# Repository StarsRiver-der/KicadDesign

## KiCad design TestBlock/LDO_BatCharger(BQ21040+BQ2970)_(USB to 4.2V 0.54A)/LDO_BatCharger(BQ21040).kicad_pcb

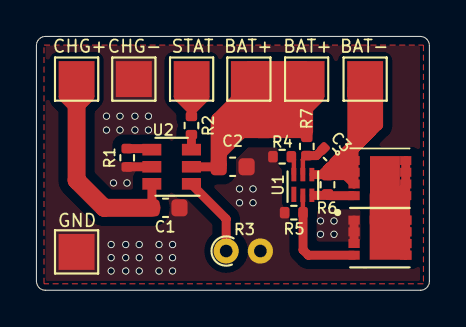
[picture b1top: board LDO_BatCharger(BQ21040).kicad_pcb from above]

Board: 2 copper layers, 21.8 x 14.1 mm, 21 parts (0 on the bottom side), 13 nets.

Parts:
C1, C2: 1uF; C_0603_1608Metric
C3: 0.1uF; C_0402_1005Metric
J1, J2, J3, J4, J5, J6, J7: Conn_01x01; TestPoint_Pad_2.0x2.0mm
R1, R2: 1K; R_0402_1005Metric
R3: 103AT-2; R_Axial_DIN0204_L3.6mm_D1.6mm_P1.90mm_Vertical
R4: 2.2k; R_0402_1005Metric
R5: 5.1M; R_0402_1005Metric
R6: 5.1m; R_0402_1005Metric
R7: 330R; R_0402_1005Metric
U1: BQ2970; WSON-6_1.5x1.5mm_P0.5mm
U2: BQ21040; SOT-23-6
U3, U4: CSD16406Q3

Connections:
Adapter+: C1.1, J2.1, U2.6 (VIN)
BAT+: C2.1, J3.1, J5.1, R7.1, U2.2 (Vout)
BAT-: C3.2, J6.1, R6.2, U1.4 (VSS), U4.1, U4.2, U4.3
ChargeLight-: J4.1, R2.2
GND: C1.2, C2.2, J1.1, J7.1, R1.2, R3.2, R4.2, R5.2, U2.5 (GND), U3.1, U3.2, U3.3
unnamed: C3.1, R7.2, U1.5 (BAT)
unnamed: R1.1, U2.4 (ISET)
unnamed: R2.1, U2.3 (~CHG)
unnamed: R3.1, U2.1 (TS)
unnamed: R4.1, U1.6 (V-)
unnamed: R5.1, U1.2 (COUT), U3.4
unnamed: R6.1, U1.3 (DOUT), U4.4
unnamed: U3.5, U3.6, U3.7, U3.8, U4.5, U4.6, U4.7, U4.8

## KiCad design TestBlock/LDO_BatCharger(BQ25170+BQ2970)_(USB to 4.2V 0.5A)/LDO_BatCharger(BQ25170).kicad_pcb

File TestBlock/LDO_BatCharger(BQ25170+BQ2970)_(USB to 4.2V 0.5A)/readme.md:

# 4.6V-5.7V 输入的 DCDC 锂电池充放电模块
* 工作温度：0-45℃
* 支持5V/VBUS适配器输入
* 截止充电电压4.4V
* 截止放电电压2.8V

# 原理
见说明手册

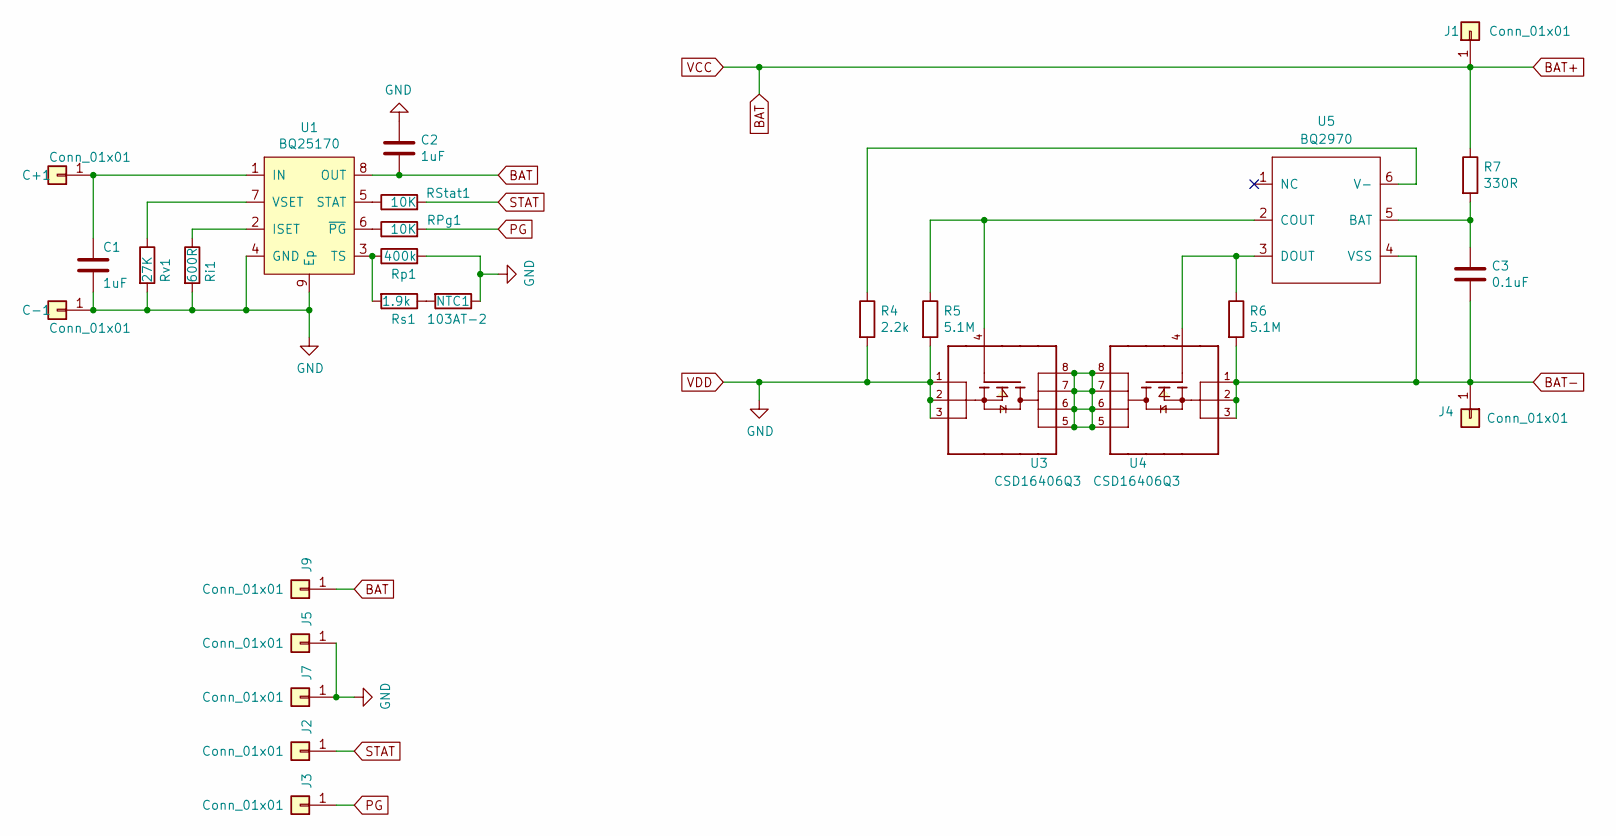
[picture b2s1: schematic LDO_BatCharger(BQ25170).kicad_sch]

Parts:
C1, C2: 1uF; C_0402_1005Metric
C3: 0.1uF; C_0402_1005Metric
C+1: Conn_01x01; TestPoint_Pad_2.0x2.0mm
C-1: Conn_01x01; TestPoint_Pad_2.0x2.0mm
J1, J2, J3, J4, J5, J7, J9: Conn_01x01; TestPoint_Pad_2.0x2.0mm
NTC1: 103AT-2; R_Axial_DIN0204_L3.6mm_D1.6mm_P1.90mm_Vertical
R4: 2.2k; R_0402_1005Metric
R5, R6: 5.1M; R_0402_1005Metric
R7: 330R; R_0402_1005Metric
RPg1: 10K; R_0402_1005Metric
RStat1: 10K; R_0402_1005Metric
Ri1: 600R; R_0402_1005Metric
Rp1: 400k; R_0402_1005Metric
Rs1: 1.9k; R_0402_1005Metric
Rv1: 27K; R_0402_1005Metric
U1: BQ25170; WSON-8-1EP_2x2mm_P0.5mm_EP0.9x1.6mm_ThermalVias
U3, U4: CSD16406Q3
U5: BQ2970; WSON-6_1.5x1.5mm_P0.5mm

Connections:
BAT: C2.2, J1.1, J9.1, R7.1, U1.8 (OUT)
BAT-: C3.2, J4.1, R6.2, U4.1, U4.2, U4.3, U5.4 (VSS)
unnamed: C3.1, R7.2, U5.5 (BAT)
unnamed: C1.1, C+1.1, U1.1 (IN)
unnamed: NTC1.2, Rs1.1
unnamed: R4.1, U5.6 (V-)
unnamed: R5.1, U3.4, U5.2 (COUT)
unnamed: R6.1, U4.4, U5.3 (DOUT)
unnamed: RPg1.1, U1.6 (~PG)
unnamed: RStat1.1, U1.5 (STAT)
unnamed: Ri1.1, U1.2 (ISET)
unnamed: Rp1.1, Rs1.2, U1.3 (TS)
unnamed: Rv1.1, U1.7 (VSET)
unnamed: U3.5, U3.6, U3.7, U3.8, U4.5, U4.6, U4.7, U4.8
PG: J3.1, RPg1.2
STAT: J2.1, RStat1.2
VDD: C1.2, C2.1, C-1.1, J5.1, J7.1, NTC1.1, R4.2, R5.2, Ri1.2, Rp1.2, Rv1.2, U1.4 (GND), U1.9 (Ep), U3.1, U3.2, U3.3

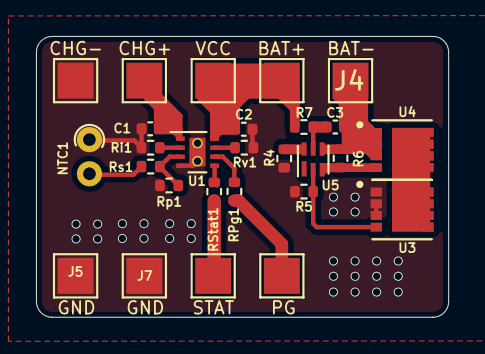
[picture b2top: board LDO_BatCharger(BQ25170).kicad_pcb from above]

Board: 2 copper layers, 22.9 x 15.6 mm, 27 parts (0 on the bottom side), 17 nets.
